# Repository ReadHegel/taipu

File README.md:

# Taipu

Taipu is a highly ergonomic, split mechanical Bluetooth keyboard I designed as a DIY project. My goal was to make it look 'barebone' with as much components visible just because I like it. I designed it with Polish language users in mind.

## Features

- Ergonomic Split Design

- Highly Customizable ZMK Layout (https://nickcoutsos.github.io/keymap-editor/)

- Wireless Connectivity

- Barebones Aesthetic

- Polish-Language Optimized

###  Ergogen 

In the `./ergogen/` directory contain the ergogen configuration of taipu. It generates the pcb with out traces and stl files needed to 3d print the case. The kicad handles cicurity of pcb (`./kicad/` directory).

### Firmware 

For firmware I have use ZMK framework. The configuration is avaiable `./taipu-zmk-config/`. Ready compiled firmware files one can find at the Github Action page on the `taipu-zmk-config` submodule.

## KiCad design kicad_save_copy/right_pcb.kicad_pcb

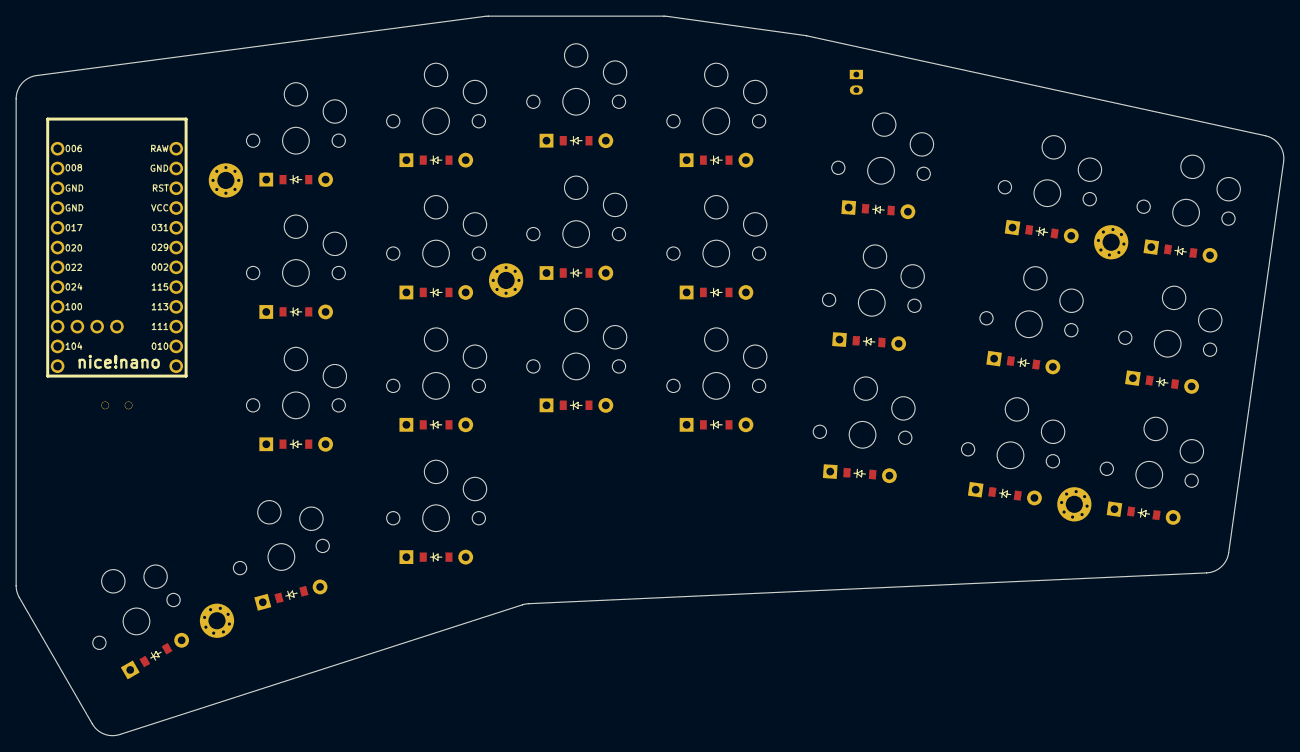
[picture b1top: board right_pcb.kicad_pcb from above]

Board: 2 copper layers, 162.9 x 92.4 mm, 56 parts (0 on the bottom side), 38 nets, no tracks yet.

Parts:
D1, D2, D3, D4, D5, D6, D7, D8, D9, D10, D11, D12, D13, D14, D15, D16, D17, D18, D19, D20, D21, D22, D23, D24: ComboDiode
JST1: JST_PH_S2B-PH-K_02x2.00mm_Angled
MCU1: nice_nano
S1, S2, S3, S4, S5, S6, S7, S8, S9, S10, S11, S12, S13, S14, S15, S16, S17, S18, S19, S20, S21, S22, S23, S24: PG1350
T1: SPDT_C128955
_1, _2, _3, _4, _5: MountingHole_2.2mm_M2_Pad_Via

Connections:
GND: JST1.2, MCU1.3, MCU1.4, MCU1.23
P002: D1.1, D4.1, D7.1, D10.1, D13.1, D17.1, D20.1, MCU1.18
P011: MCU1.10, S17.1, S18.1, S19.1, S23.1
P017: MCU1.5, S1.1, S2.1, S3.1
P020: MCU1.6, S4.1, S5.1, S6.1
P022: MCU1.7, S7.1, S8.1, S9.1
P024: MCU1.8, S10.1, S11.1, S12.1
P029: D2.1, D5.1, D8.1, D11.1, D14.1, D18.1, D21.1, MCU1.19
P031: D3.1, D6.1, D9.1, D12.1, D15.1, D19.1, D22.1, MCU1.20
P100: MCU1.9, S13.1, S14.1, S15.1, S16.1
P104: MCU1.11, S20.1, S21.1, S22.1, S24.1
P115: D16.1, D23.1, D24.1, MCU1.17
RAW: MCU1.24, T1.2
mirror_clone_outer_bottom: D1.2, S1.2
mirror_clone_outer_home: D2.2, S2.2
mirror_clone_outer_top: D3.2, S3.2
mirror_index_bottom: D17.2, S17.2
mirror_index_home: D18.2, S18.2
mirror_index_mod: D16.2, S16.2
mirror_index_top: D19.2, S19.2
mirror_inner_bottom: D20.2, S20.2
mirror_inner_home: D21.2, S21.2
mirror_inner_top: D22.2, S22.2
mirror_layer_cluster: D23.2, S23.2
mirror_middle_bottom: D13.2, S13.2
mirror_middle_home: D14.2, S14.2
mirror_middle_top: D15.2, S15.2
mirror_outer_bottom: D4.2, S4.2
mirror_outer_home: D5.2, S5.2
mirror_outer_top: D6.2, S6.2
mirror_pinky_bottom: D7.2, S7.2
mirror_pinky_home: D8.2, S8.2
mirror_pinky_top: D9.2, S9.2
mirror_ring_bottom: D10.2, S10.2
mirror_ring_home: D11.2, S11.2
mirror_ring_top: D12.2, S12.2
mirror_space_cluster: D24.2, S24.2
pos: JST1.1, T1.1

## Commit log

2025-07-15 init
2025-07-20 mounting holes and net
2025-07-20 routing
2025-07-22 better batery placement
2025-07-25 add logo
2025-08-07 drills and simple case
2025-08-13 fix workflow
2025-08-13 add submodule
2025-08-13 add zmk
2025-08-13 sym link solving
2025-08-13 repo refactor
2025-08-13 workflow
2025-08-21 add pcb standoff next to the wall
2025-08-21 sync zmk
2025-09-06 fix case buffer for 3d printing
2025-09-17 add readme
